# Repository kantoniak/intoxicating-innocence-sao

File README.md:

# Intoxicating Innocence SAO

A blinky [SAO (Simple Add-on/Shitty Add-on)](https://hackaday.io/project/52950-shitty-add-ons/log/159806-introducing-the-shitty-add-on-v169bis-standard) celebrating [Dagoth Ur](https://en.uesp.net/wiki/Lore:Dagoth_Ur), the beloved villain of [TES 3: Morrowind (2002)](https://en.uesp.net/wiki/Morrowind:Morrowind).

> [[Listen on YouTube](https://www.youtube.com/watch?v=fsXzoQte2kw)]: What a fool you are. I'm a god. How can you kill a god? What a grand and intoxicating innocence. How could you be so naive? There is no escape. No Recall or Intervention can work in this place. Come. Lay down your weapons. It is not too late for my mercy. — *Dagoth Ur*

The project consists of:
* PCB design (see [hardware/](./hardware/))
* Mask model:
  * Front model (to be shared, [enclosure/mask/](./enclosure/mask/))
  * Negative volume, an envelope for the PCB and mounting elements (see [enclosure/pcb-envelope/](./enclosure/pcb-envelope/))

Some components are available in the repository only as scripts that generate resources.

## Assembly

It's quick - you only need a screwdriver (Hexagonal M2 or Torx 6) and light soldering.

> [!IMPORTANT]
> Before starting, check the contents of your kit. I have spares if anything is missing or damaged.
> You should have:
> * 3D‑printed mask model
> * Custom PCB
> * 1 shrouded SAO connector
> * 3 red LEDs
> * 1 M2 screw

1. Solder the LEDs with the red emitters **on the front side (with the quote)** (the short leg is negative pole and goes through the square GND pad).
2. Solder the SAO connector **on the back side (with the SMD components)**.
3. Insert the PCB into the 3D-printed mask, LEDs first. Screw the PCB in place.

> [!TIP]
> The programming pads are on a 0.1" grid for easy access.
> You only need `3V3`, `GND`, and `SWIO`; they are in a straight line.
>
> For flashing, use PlatformIO with the open‑source
> **[minilink](https://github.com/cnlohr/ch32fun/blob/master/minichlink/README.md)** programmer.
> Elliot also wrote a [Pico‑based flasher](https://github.com/hexagon5un/pico_ch32v003_prog/) (not tested by me).

## PCB

The PCB was designed in KiCad. See `hardware/` for the source files and releases for generated outputs.

<p align="center">
  
</p>

## License

This project is licensed under the `CERN-OHL-S-2.0` license - see the [LICENSE](LICENSE) file for details.

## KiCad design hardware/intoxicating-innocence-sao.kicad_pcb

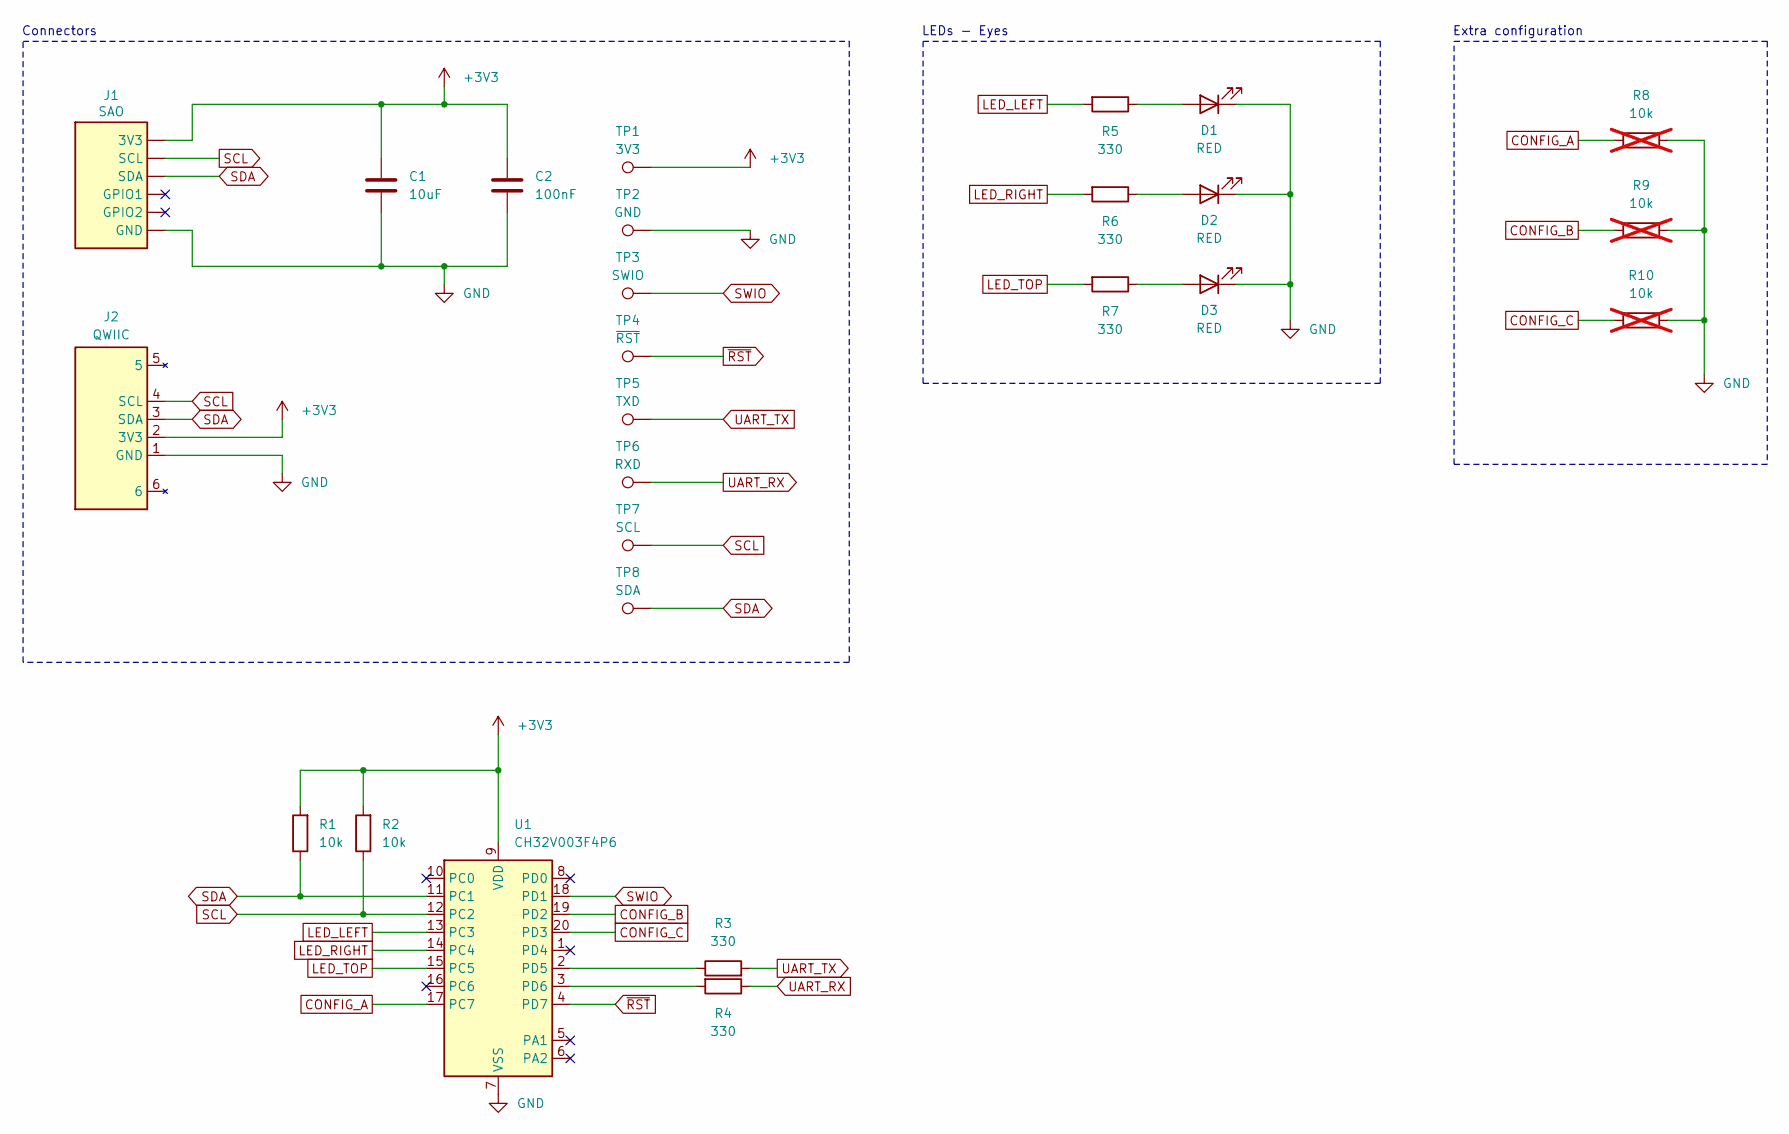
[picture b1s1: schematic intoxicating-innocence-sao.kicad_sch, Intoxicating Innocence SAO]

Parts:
C1: 10uF; C_0603_1608Metric_Pad1.08x0.95mm_HandSolder; LCSC Part # C109455
C2: 100nF; C_0603_1608Metric_Pad1.08x0.95mm_HandSolder; LCSC Part # C14663
D1, D2, D3: RED; LED_D3.0mm
J1: SAO; SAO_Header_Addon_Side
J2: QWIIC; JST_SH_SM04B-SRSS-TB_1x04-1MP_P1.00mm_Horizontal; Manufacturer Part SM04B-SRSS-TB(LF)(SN); LCSC Part # C160404
R1, R2: 10k; R_0603_1608Metric_Pad0.98x0.95mm_HandSolder; LCSC Part # C25804
R3, R4, R5, R6, R7: 330; R_0603_1608Metric_Pad0.98x0.95mm_HandSolder; LCSC Part # C23345
R8, R9, R10: 10k; R_0603_1608Metric_Pad0.98x0.95mm_HandSolder; not fitted
TP1: 3V3; TestPoint_Pad_D1.5mm
TP2: GND; TestPoint_Pad_D1.5mm
TP3: SWIO; TestPoint_Pad_D1.5mm
TP4: ~{RST}; TestPoint_Pad_D1.5mm
TP5: TXD; TestPoint_Pad_D1.5mm
TP6: RXD; TestPoint_Pad_D1.5mm
TP7: SCL; TestPoint_Pad_D1.5mm
TP8: SDA; TestPoint_Pad_D1.5mm
U1: CH32V003F4P6; TSSOP-20_4.4x6.5mm_P0.65mm; LCSC Part # C5187096

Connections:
+3V3: C1.1, C2.1, J1.6 (3V3), J2.2 (3V3), R1.2, R2.2, TP1.1 (1_1), U1.9 (VDD)
CONFIG_A: R8.1, U1.17 (PC7)
CONFIG_B: R9.2, U1.19 (PD2)
CONFIG_C: R10.2, U1.20 (PD3)
GND: C1.2, C2.2, D1.1 (K), D2.1 (K), D3.1 (K), J1.1 (GND), J2.1 (GND), R8.2, R9.1, R10.1, TP2.1 (1_1), U1.7 (VSS)
LED_LEFT: R5.2, U1.13 (PC3)
LED_RIGHT: R6.2, U1.14 (PC4)
LED_TOP: R7.2, U1.15 (PC5)
unnamed: D1.2 (A), R5.1
unnamed: D2.2 (A), R6.1
unnamed: D3.2 (A), R7.1
unnamed: R3.1, U1.2 (PD5)
unnamed: R4.2, U1.3 (PD6)
SCL: J1.2 (SCL), J2.4 (SCL), R2.1, TP7.1 (1_1), U1.12 (PC2)
SDA: J1.5 (SDA), J2.3 (SDA), R1.1, TP8.1 (1_1), U1.11 (PC1)
SWIO: TP3.1 (1_1), U1.18 (PD1)
UART_RX: R4.1, TP6.1 (1_1)
UART_TX: R3.2, TP5.1 (1_1)
~RST: TP4.1 (1_1), U1.4 (PD7)

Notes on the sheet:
Extra configuration
Connectors
LEDs - Eyes

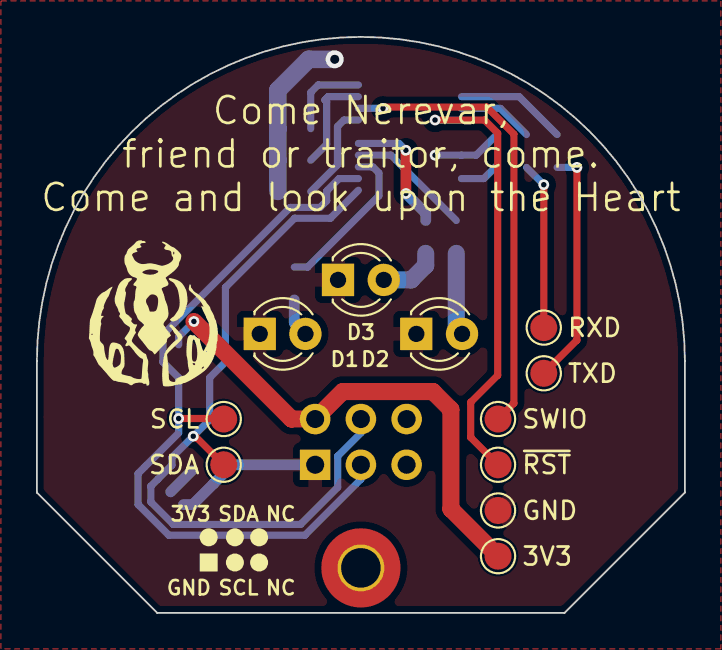
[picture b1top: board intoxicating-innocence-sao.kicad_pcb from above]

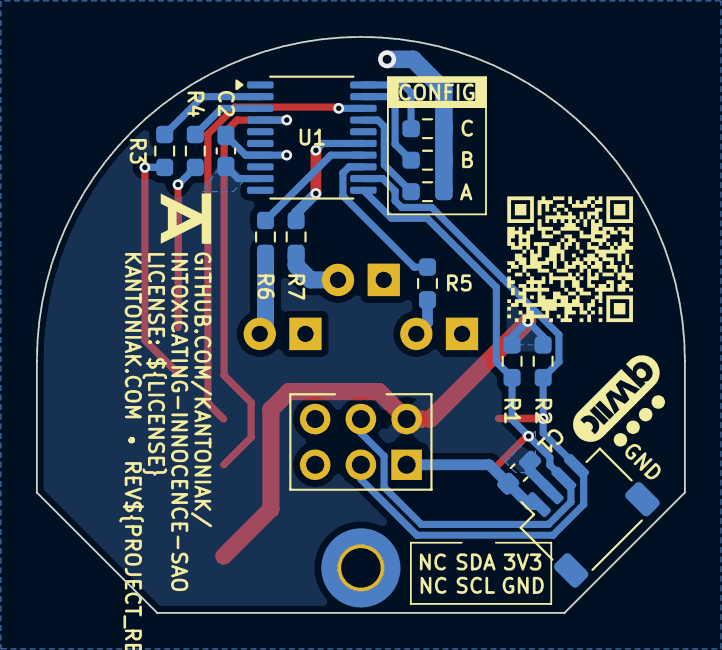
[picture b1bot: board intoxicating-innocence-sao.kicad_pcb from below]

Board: 2 copper layers, 36.0 x 32.0 mm, 27 parts (16 on the bottom side), 19 nets.

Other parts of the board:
QWIIC_Front: QWIIC_Front; qwiic_logo

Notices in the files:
parts and their libraries:
LICENSE: CERN-OHL-S-2.0
